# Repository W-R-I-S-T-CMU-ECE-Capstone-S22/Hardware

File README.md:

# Hardware

Eagle schematics for WRIST

https://drive.google.com/drive/u/1/folders/1LIEhgLYjapwJlwbO2dgOSEpxd2zEnNpc

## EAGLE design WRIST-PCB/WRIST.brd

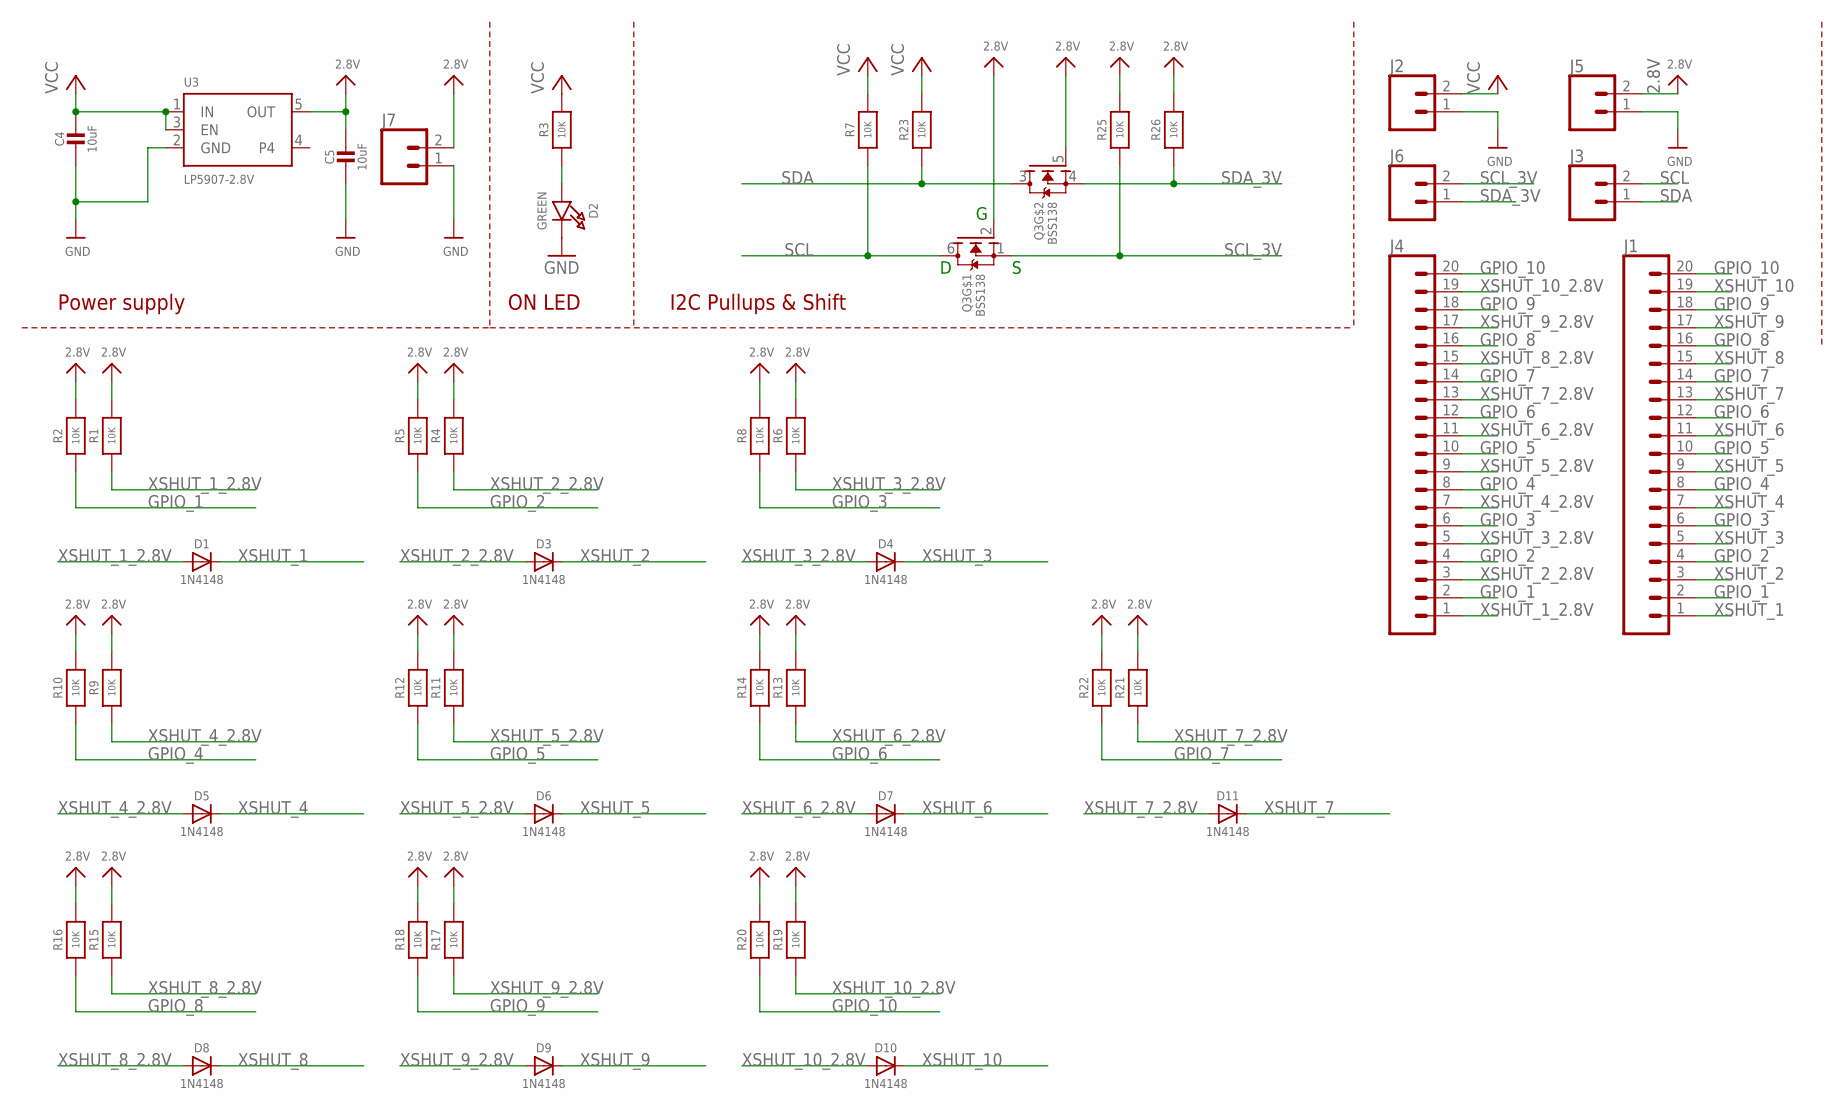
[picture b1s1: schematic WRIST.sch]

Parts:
C4, C5: 10uF; 0805-NO
D1, D3, D4, D5, D6, D7, D8, D9, D10, D11: 1N4148; SOD-323
D2: GREEN; CHIPLED_0603_NOOUTLINE
J1, J4: CONN_20NOSILK; 1X20_NOSILK
J2, J3, J5, J6, J7: CONN_021X02_NO_SILK; 1X02_NO_SILK
Q3: BSS138; SOT363
R1, R2, R3, R4, R5, R6, R7, R8, R9, R10, R11, R12, R13, R14, R15, R16, R17, R18, R19, R20, R21, R22, R23, R25, R26: 10K; 0603-NO
U3: LP5907-2.8V; SOT23-5

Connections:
2.8V: C5.1, J5.2, J7.2, Q3.2 (G), Q3.5 (G), R1.2, R2.2, R4.2, R5.2, R6.2, R8.2, R9.2, R10.2, R11.2, R12.2, R13.2, R14.2, R15.2, R16.2, R17.2, R18.2, R19.2, R20.2, R21.2, R22.2, R25.2, R26.2, U3.5 (OUT)
GND: C4.2, C5.2, D2.C, J2.1, J5.1, J7.1, U3.2 (GND)
GPIO_1: J1.2, J4.2, R2.1
GPIO_2: J1.4, J4.4, R5.1
GPIO_3: J1.6, J4.6, R8.1
GPIO_4: J1.8, J4.8, R10.1
GPIO_5: J1.10, J4.10, R12.1
GPIO_6: J1.12, J4.12, R14.1
GPIO_7: J1.14, J4.14, R22.1
GPIO_8: J1.16, J4.16, R16.1
GPIO_9: J1.18, J4.18, R18.1
GPIO_10: J1.20, J4.20, R20.1
unnamed: D2.A, R3.1
SCL: J3.2, Q3.6 (D), R7.1
SCL_3V: J6.2, Q3.1 (S), R25.1
SDA: J3.1, Q3.3 (D), R23.1
SDA_3V: J6.1, Q3.4 (S), R26.1
VCC: C4.1, J2.2, R3.2, R7.2, R23.2, U3.1 (IN), U3.3 (EN)
XSHUT_1: D1.C, J1.1
XSHUT_1_2.8V: D1.A, J4.1, R1.1
XSHUT_2: D3.C, J1.3
XSHUT_2_2.8V: D3.A, J4.3, R4.1
XSHUT_3: D4.C, J1.5
XSHUT_3_2.8V: D4.A, J4.5, R6.1
XSHUT_4: D5.C, J1.7
XSHUT_4_2.8V: D5.A, J4.7, R9.1
XSHUT_5: D6.C, J1.9
XSHUT_5_2.8V: D6.A, J4.9, R11.1
XSHUT_6: D7.C, J1.11
XSHUT_6_2.8V: D7.A, J4.11, R13.1
XSHUT_7: D11.C, J1.13
XSHUT_7_2.8V: D11.A, J4.13, R21.1
XSHUT_8: D8.C, J1.15
XSHUT_8_2.8V: D8.A, J4.15, R15.1
XSHUT_9: D9.C, J1.17
XSHUT_9_2.8V: D9.A, J4.17, R17.1
XSHUT_10: D10.C, J1.19
XSHUT_10_2.8V: D10.A, J4.19, R19.1

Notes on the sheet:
I2C Pullups & Shift
ON LED
Power supply

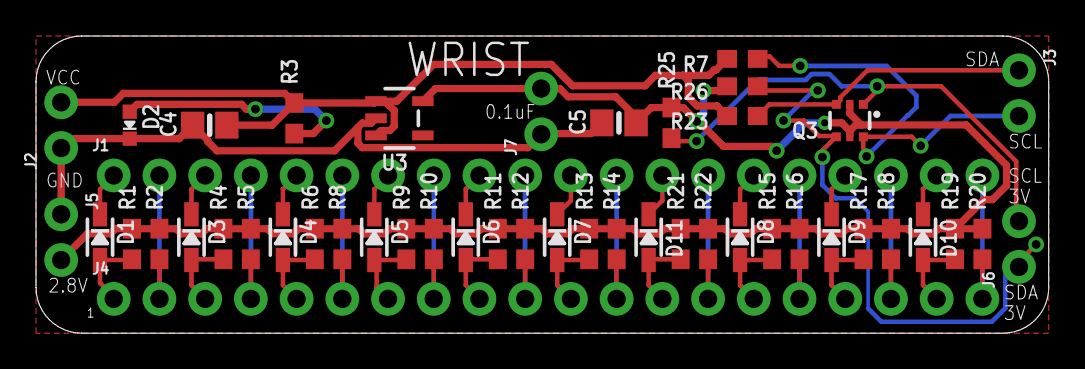
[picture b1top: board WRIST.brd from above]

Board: 2 copper layers, 56.3 x 16.5 mm, 47 parts (0 on the bottom side), 38 nets.

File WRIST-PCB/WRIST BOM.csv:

Qty,Designator,Device,Footprint,Comment,JLCPCB Part #（optional）,Description
4,"J2, J3, J5, J6",CONN_021X02_NO_SILK,1X02_NO_SILK,,,Multi connection point. Often used as Generic Header-pin footprint for 0.1 inch spaced/style header connections
2,"J1, J4",CONN_20NOSILK,1X20_NOSILK,,,Multi connection point. Often used as Generic Header-pin footprint for 0.1 inch spaced/style header connections
21,"R1, R2, R3, R4, R5, R6, R8, R7, R9, R10, R11, R12, R13, R14, R15, R16, R17, R18, R19, R20, R21, R22, R23, R25, R26",RESISTOR_0603_NOOUT,0603-NO,10K,C269701,Resistors
2,"C4, C5",CAP_CERAMIC0805-NOOUTLINE,0805-NO,10uF,C129234,Ceramic Capacitors
10,"D1, D3, D4, D5, D6, D7, D8, D9, D10, D11",DIODESOD-323,SOD-323,1N4148,C81598,Diode
1,Q3,MOSFET-N_DUAL,SOT363,BSS138,C779245,Dual N-Channel MOSFET
1,D2,LED0603_NOOUTLINE,CHIPLED_0603_NOOUTLINE,GREEN,1N4148,LED
1,U3,VREG_SOT23-5,SOT23-5,LP5907-2.8V,C80670,SOT23-5 Fixed Voltage Regulators

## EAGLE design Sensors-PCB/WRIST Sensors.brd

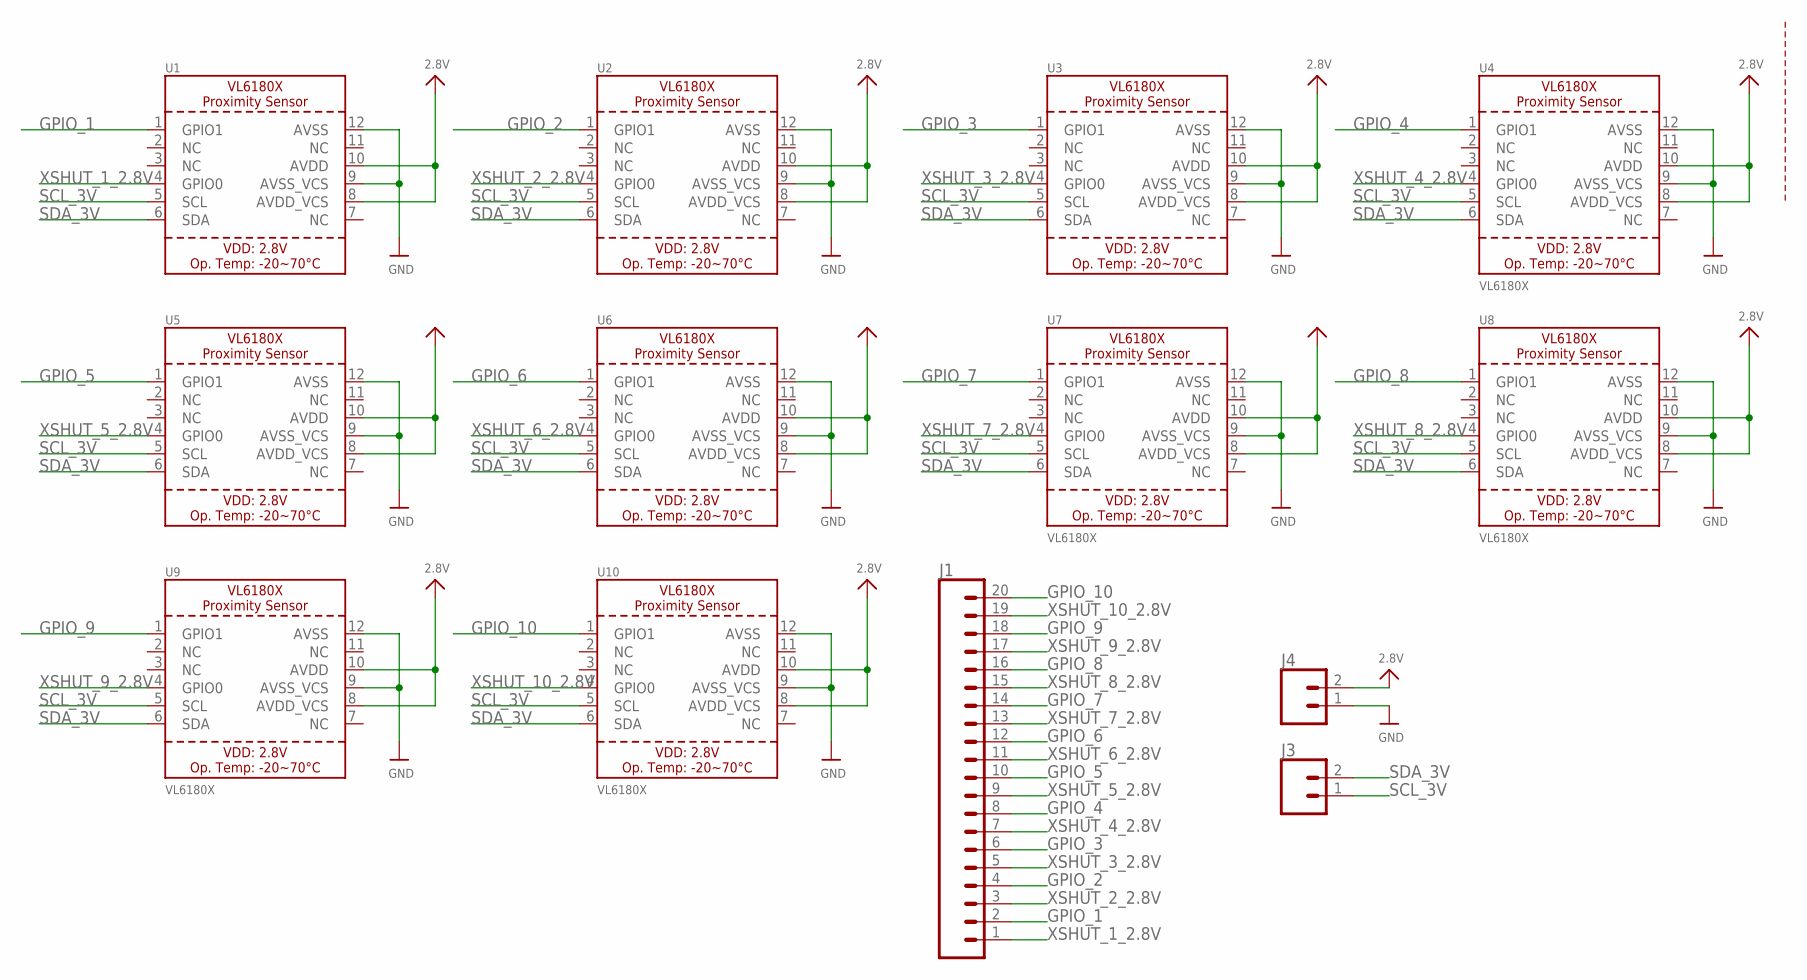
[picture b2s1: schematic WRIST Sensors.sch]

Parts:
J1: CONN_20NOSILK; 1X20_NOSILK
J3, J4: CONN_021X02_NO_SILK; 1X02_NO_SILK
U1, U2, U3, U4, U5, U6, U7, U8, U9, U10: VL6180X; VL6180

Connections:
2.8V: J4.2, U1.8 (AVDD_VCS), U1.10 (AVDD), U2.8 (AVDD_VCS), U2.10 (AVDD), U3.8 (AVDD_VCS), U3.10 (AVDD), U4.8 (AVDD_VCS), U4.10 (AVDD), U5.8 (AVDD_VCS), U5.10 (AVDD), U6.8 (AVDD_VCS), U6.10 (AVDD), U7.8 (AVDD_VCS), U7.10 (AVDD), U8.8 (AVDD_VCS), U8.10 (AVDD), U9.8 (AVDD_VCS), U9.10 (AVDD), U10.8 (AVDD_VCS), U10.10 (AVDD)
GND: J4.1, U1.9 (AVSS_VCS), U1.12 (AVSS), U2.9 (AVSS_VCS), U2.12 (AVSS), U3.9 (AVSS_VCS), U3.12 (AVSS), U4.9 (AVSS_VCS), U4.12 (AVSS), U5.9 (AVSS_VCS), U5.12 (AVSS), U6.9 (AVSS_VCS), U6.12 (AVSS), U7.9 (AVSS_VCS), U7.12 (AVSS), U8.9 (AVSS_VCS), U8.12 (AVSS), U9.9 (AVSS_VCS), U9.12 (AVSS), U10.9 (AVSS_VCS), U10.12 (AVSS)
GPIO_1: J1.2, U1.1 (GPIO1)
GPIO_2: J1.4, U2.1 (GPIO1)
GPIO_3: J1.6, U3.1 (GPIO1)
GPIO_4: J1.8, U4.1 (GPIO1)
GPIO_5: J1.10, U5.1 (GPIO1)
GPIO_6: J1.12, U6.1 (GPIO1)
GPIO_7: J1.14, U7.1 (GPIO1)
GPIO_8: J1.16, U8.1 (GPIO1)
GPIO_9: J1.18, U9.1 (GPIO1)
GPIO_10: J1.20, U10.1 (GPIO1)
SCL_3V: J3.1, U1.5 (SCL), U2.5 (SCL), U3.5 (SCL), U4.5 (SCL), U5.5 (SCL), U6.5 (SCL), U7.5 (SCL), U8.5 (SCL), U9.5 (SCL), U10.5 (SCL)
SDA_3V: J3.2, U1.6 (SDA), U2.6 (SDA), U3.6 (SDA), U4.6 (SDA), U5.6 (SDA), U6.6 (SDA), U7.6 (SDA), U8.6 (SDA), U9.6 (SDA), U10.6 (SDA)
XSHUT_1_2.8V: J1.1, U1.4 (GPIO0)
XSHUT_2_2.8V: J1.3, U2.4 (GPIO0)
XSHUT_3_2.8V: J1.5, U3.4 (GPIO0)
XSHUT_4_2.8V: J1.7, U4.4 (GPIO0)
XSHUT_5_2.8V: J1.9, U5.4 (GPIO0)
XSHUT_6_2.8V: J1.11, U6.4 (GPIO0)
XSHUT_7_2.8V: J1.13, U7.4 (GPIO0)
XSHUT_8_2.8V: J1.15, U8.4 (GPIO0)
XSHUT_9_2.8V: J1.17, U9.4 (GPIO0)
XSHUT_10_2.8V: J1.19, U10.4 (GPIO0)

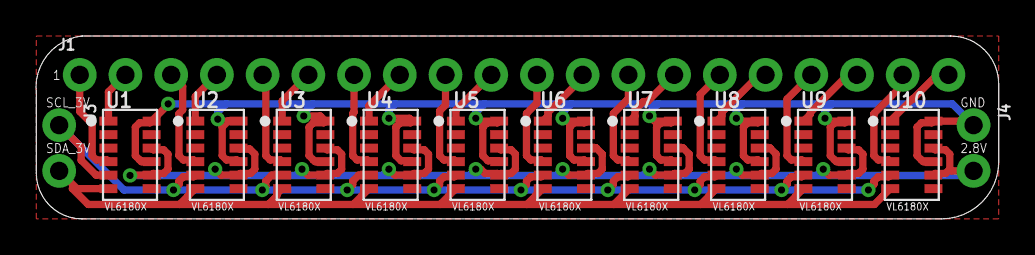
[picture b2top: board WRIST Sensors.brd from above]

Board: 2 copper layers, 53.5 x 10.2 mm, 13 parts (0 on the bottom side), 24 nets.

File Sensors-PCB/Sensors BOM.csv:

"Qty";"Value";"Device";"Package";"Parts";"Description";"";
"2";"";"CONN_021X02_NO_SILK";"1X02_NO_SILK";"J3, J4";"Multi connection point. Often used as Generic Header-pin footprint for 0.1 inch spaced/style header connections";"";
"1";"";"CONN_20NOSILK";"1X20_NOSILK";"J1";"Multi connection point. Often used as Generic Header-pin footprint for 0.1 inch spaced/style header connections";"";
"10";"VL6180X";"VL6180X";"VL6180";"U1, U2, U3, U4, U5, U6, U7, U8, U9, U10";"VL6180x Proximity and Light Sensor with Gesture Recognition";"";

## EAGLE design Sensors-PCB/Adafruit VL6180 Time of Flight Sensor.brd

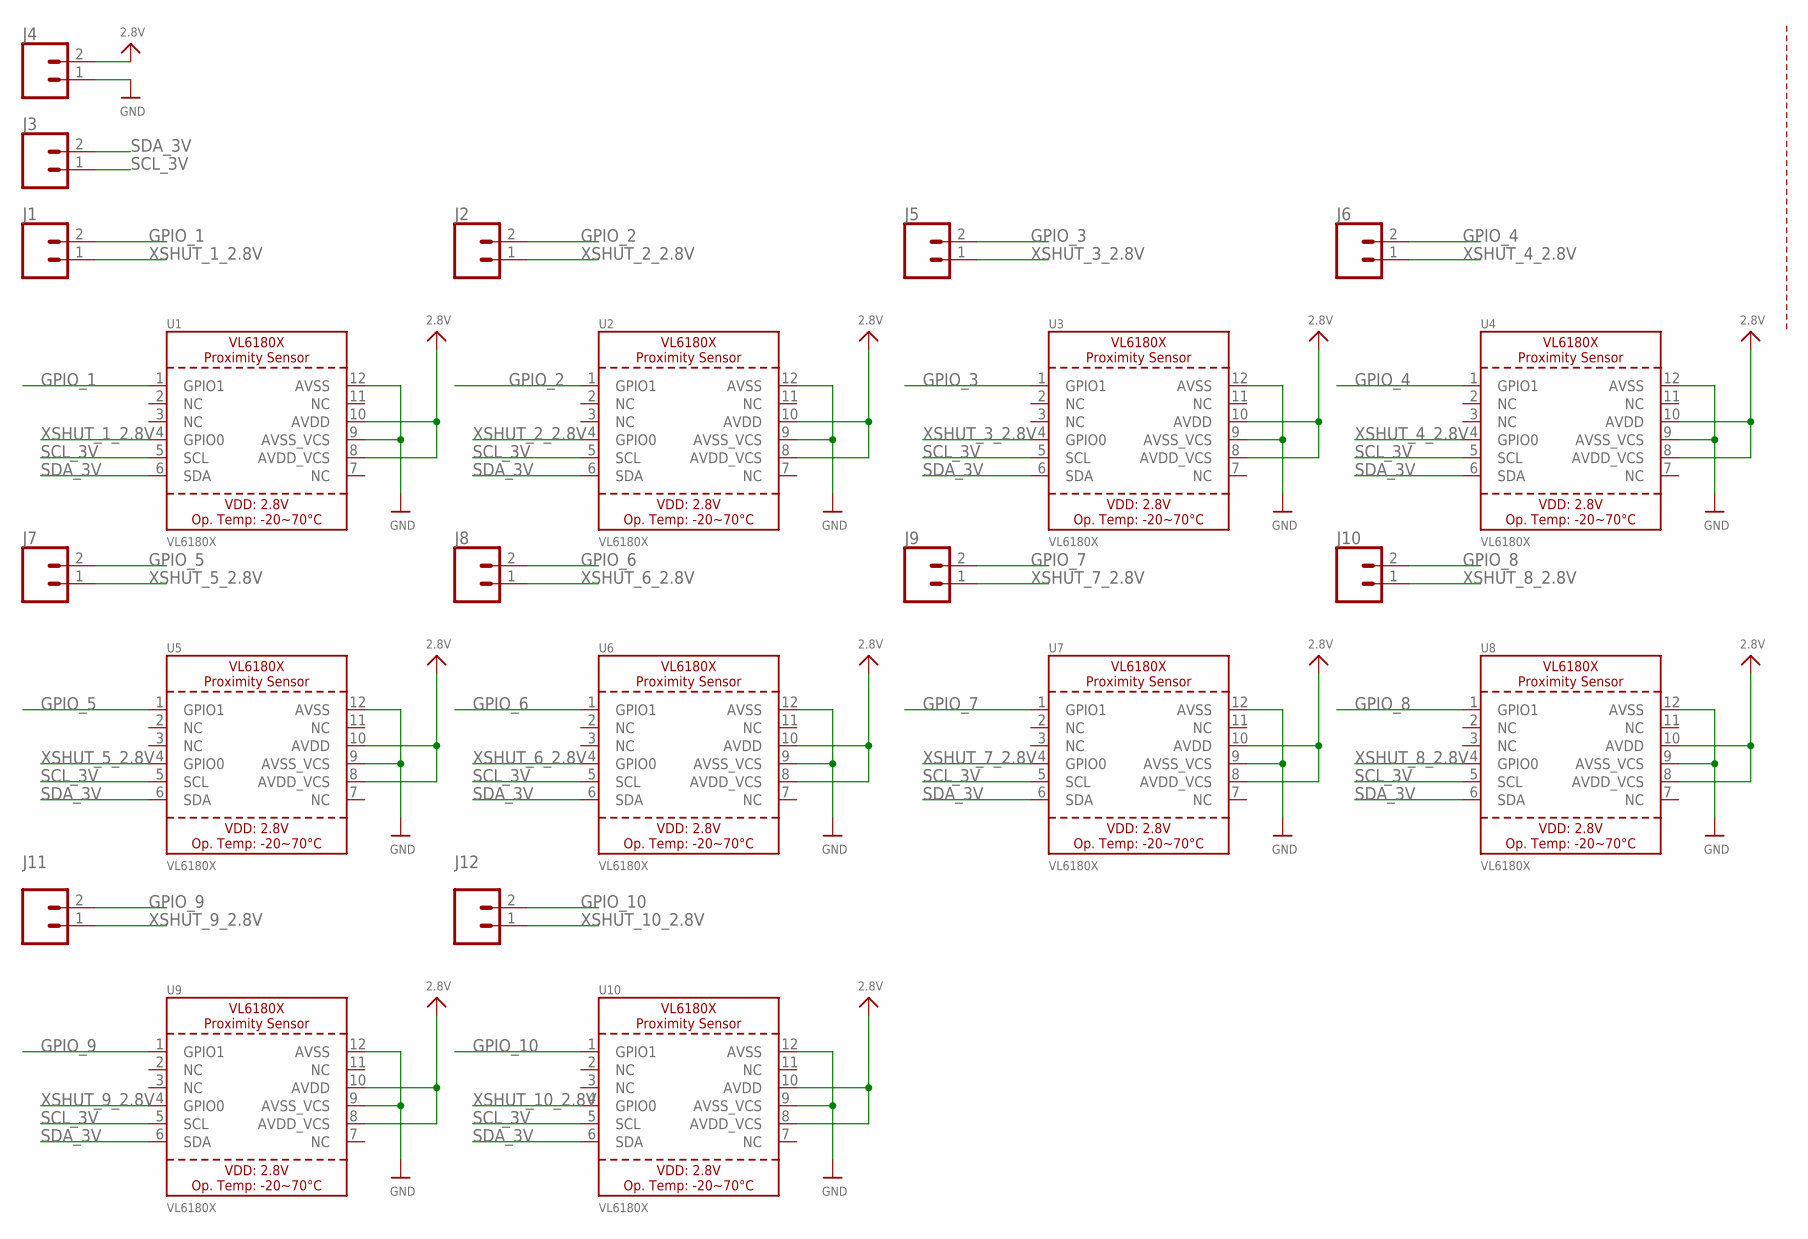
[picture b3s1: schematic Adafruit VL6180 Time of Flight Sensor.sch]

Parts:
J1, J2, J3, J4, J5, J6, J7, J8, J9, J10, J11, J12: CONN_021X02_NO_SILK; 1X02_NO_SILK
U1, U2, U3, U4, U5, U6, U7, U8, U9, U10: VL6180X; VL6180

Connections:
2.8V: J4.2, U1.8 (AVDD_VCS), U1.10 (AVDD), U2.8 (AVDD_VCS), U2.10 (AVDD), U3.8 (AVDD_VCS), U3.10 (AVDD), U4.8 (AVDD_VCS), U4.10 (AVDD), U5.8 (AVDD_VCS), U5.10 (AVDD), U6.8 (AVDD_VCS), U6.10 (AVDD), U7.8 (AVDD_VCS), U7.10 (AVDD), U8.8 (AVDD_VCS), U8.10 (AVDD), U9.8 (AVDD_VCS), U9.10 (AVDD), U10.8 (AVDD_VCS), U10.10 (AVDD)
GND: J4.1, U1.9 (AVSS_VCS), U1.12 (AVSS), U2.9 (AVSS_VCS), U2.12 (AVSS), U3.9 (AVSS_VCS), U3.12 (AVSS), U4.9 (AVSS_VCS), U4.12 (AVSS), U5.9 (AVSS_VCS), U5.12 (AVSS), U6.9 (AVSS_VCS), U6.12 (AVSS), U7.9 (AVSS_VCS), U7.12 (AVSS), U8.9 (AVSS_VCS), U8.12 (AVSS), U9.9 (AVSS_VCS), U9.12 (AVSS), U10.9 (AVSS_VCS), U10.12 (AVSS)
GPIO_1: J1.2, U1.1 (GPIO1)
GPIO_2: J2.2, U2.1 (GPIO1)
GPIO_3: J5.2, U3.1 (GPIO1)
GPIO_4: J6.2, U4.1 (GPIO1)
GPIO_5: J7.2, U5.1 (GPIO1)
GPIO_6: J8.2, U6.1 (GPIO1)
GPIO_7: J9.2, U7.1 (GPIO1)
GPIO_8: J10.2, U8.1 (GPIO1)
GPIO_9: J11.2, U9.1 (GPIO1)
GPIO_10: J12.2, U10.1 (GPIO1)
SCL_3V: J3.1, U1.5 (SCL), U2.5 (SCL), U3.5 (SCL), U4.5 (SCL), U5.5 (SCL), U6.5 (SCL), U7.5 (SCL), U8.5 (SCL), U9.5 (SCL), U10.5 (SCL)
SDA_3V: J3.2, U1.6 (SDA), U2.6 (SDA), U3.6 (SDA), U4.6 (SDA), U5.6 (SDA), U6.6 (SDA), U7.6 (SDA), U8.6 (SDA), U9.6 (SDA), U10.6 (SDA)
XSHUT_1_2.8V: J1.1, U1.4 (GPIO0)
XSHUT_2_2.8V: J2.1, U2.4 (GPIO0)
XSHUT_3_2.8V: J5.1, U3.4 (GPIO0)
XSHUT_4_2.8V: J6.1, U4.4 (GPIO0)
XSHUT_5_2.8V: J7.1, U5.4 (GPIO0)
XSHUT_6_2.8V: J8.1, U6.4 (GPIO0)
XSHUT_7_2.8V: J9.1, U7.4 (GPIO0)
XSHUT_8_2.8V: J10.1, U8.4 (GPIO0)
XSHUT_9_2.8V: J11.1, U9.4 (GPIO0)
XSHUT_10_2.8V: J12.1, U10.4 (GPIO0)

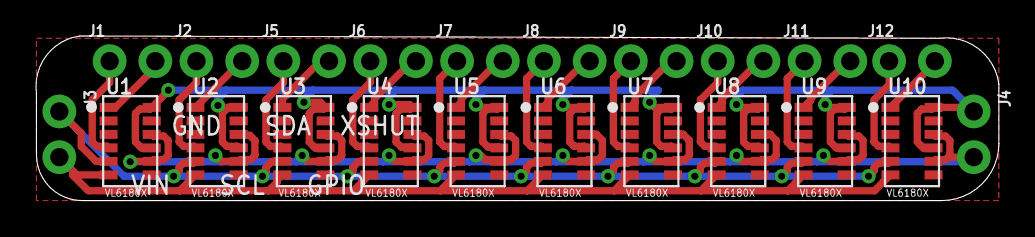
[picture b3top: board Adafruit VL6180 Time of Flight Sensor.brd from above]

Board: 2 copper layers, 53.5 x 9.1 mm, 22 parts (0 on the bottom side), 24 nets.

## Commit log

2022-02-09 remove some misc files
2022-02-09 add eagle gitignore
2022-02-11 add 20 pin header and rename board
2022-02-11 start wrist pcb (support stuff)
2022-02-11 progress
2022-02-11 finish wrist pcb
2022-02-11 add gerber files
2022-02-13 edit gerber files
2022-02-13 edit sensors
2022-02-15 update pcb through holes and design
2022-02-15 add bom and cpl
2022-02-15 add text to wrist
2022-02-16 update wrist pcb
2022-02-19 replace smt capacitor with holes

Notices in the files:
parts and their libraries:
microbuilder: This work is placed in the public domain, and may be freely used for commercial and non-commercial work with the following conditions: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
SparkFun-Connectors: Licensing: Creative Commons ShareAlike 4.0 International - https://creativecommons.org/licenses/by-sa/4.0
